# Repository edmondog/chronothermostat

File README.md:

# chronothermostat
Homebrewed room by room themperature control

Very rough i2c control for the temperature sensor (texas tmp 102 http://www.ti.com.cn/cn/lit/ds/symlink/tmp102.pdf)
The board has:
4 digit 7seg led display
1 encoder
1 pushbutton
485 serial interface
2 tempeature sensors
1 AC triac switch
ATMEGA328p cpu

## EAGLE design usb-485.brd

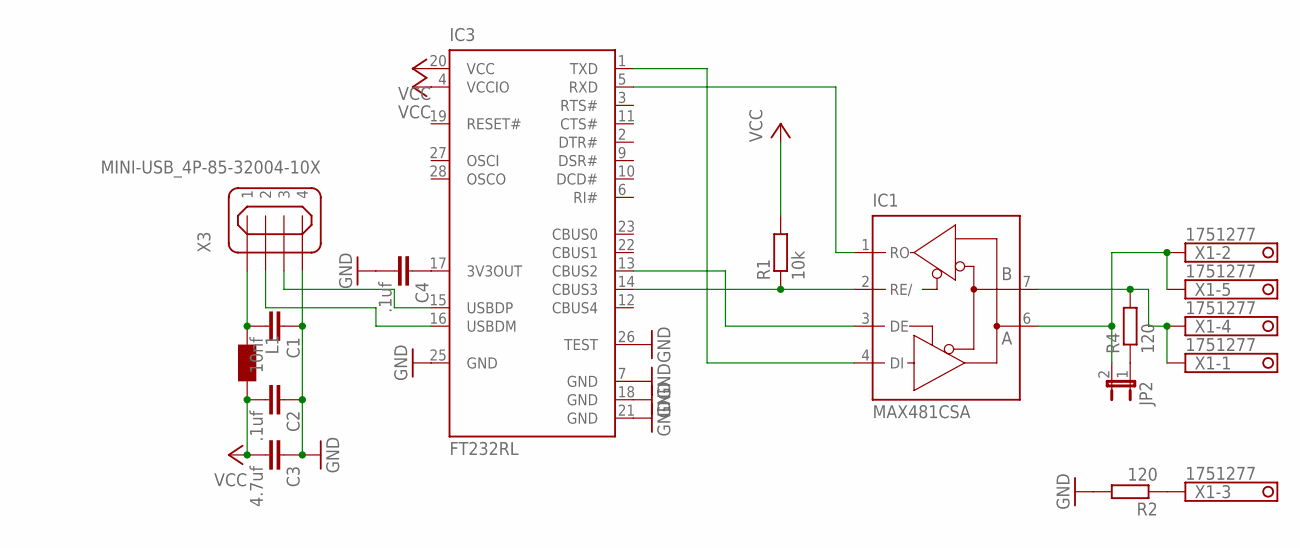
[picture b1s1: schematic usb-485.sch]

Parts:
C1: 10nf; C0805
C2, C4: .1uf; C1206
C3: 4.7uf; C1206
IC1: MAX481CSA; SO08
IC3: FT232RL; SSOP28
JP2: JP1E; JP1
L1: WE-CBF_1206; 1206
R1: 10k; 0207/10
R2, R4: 120; 0207/10
X1: 1751277
X3: MINI-USB_4P-85-32004-10X; 85-32004-10X

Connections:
GND: C1.1, C2.1, C3.1, C4.2, IC1.5 (GND), IC3.7 (GND), IC3.18 (GND), IC3.21 (GND), IC3.25 (GND), IC3.26 (TEST), R2.2, X3.4
unnamed: IC1.3 (DE), IC3.13 (CBUS2)
unnamed: IC1.2 (RE/), IC3.14 (CBUS3), R1.1
unnamed: IC1.7 (B), R4.2, X1.1, X1.4
unnamed: R2.1, X1.3
unnamed: JP2.1, R4.1
unnamed: C1.2, L1.1, X3.1
unnamed: IC1.6 (A), JP2.2, X1.2, X1.5
unnamed: IC3.16 (USBDM), X3.2
unnamed: IC3.15 (USBDP), X3.3
unnamed: C4.1, IC3.17 (3V3OUT)
unnamed: IC1.1 (RO), IC3.5 (RXD)
unnamed: IC1.4 (DI), IC3.1 (TXD)
VCC: C2.2, C3.2, IC1.8 (VCC), IC3.4 (VCCIO), IC3.20 (VCC), L1.2, R1.2

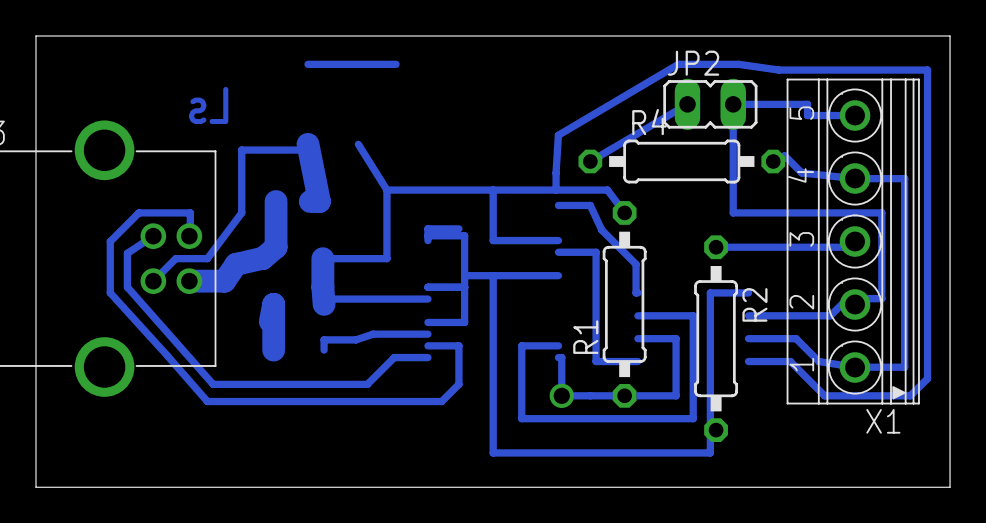
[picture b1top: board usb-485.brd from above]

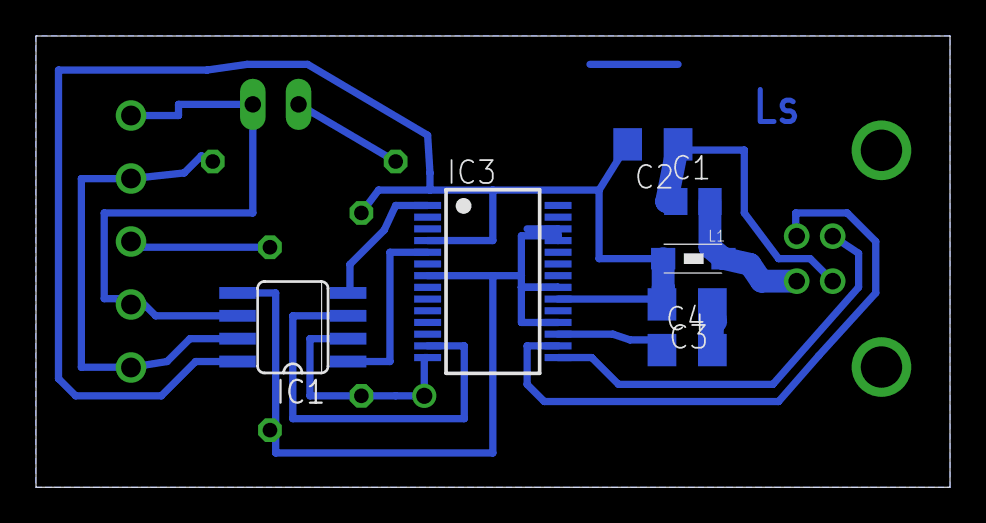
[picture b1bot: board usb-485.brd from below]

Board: 2 copper layers, 50.8 x 25.1 mm, 13 parts (7 on the bottom side), 14 nets.

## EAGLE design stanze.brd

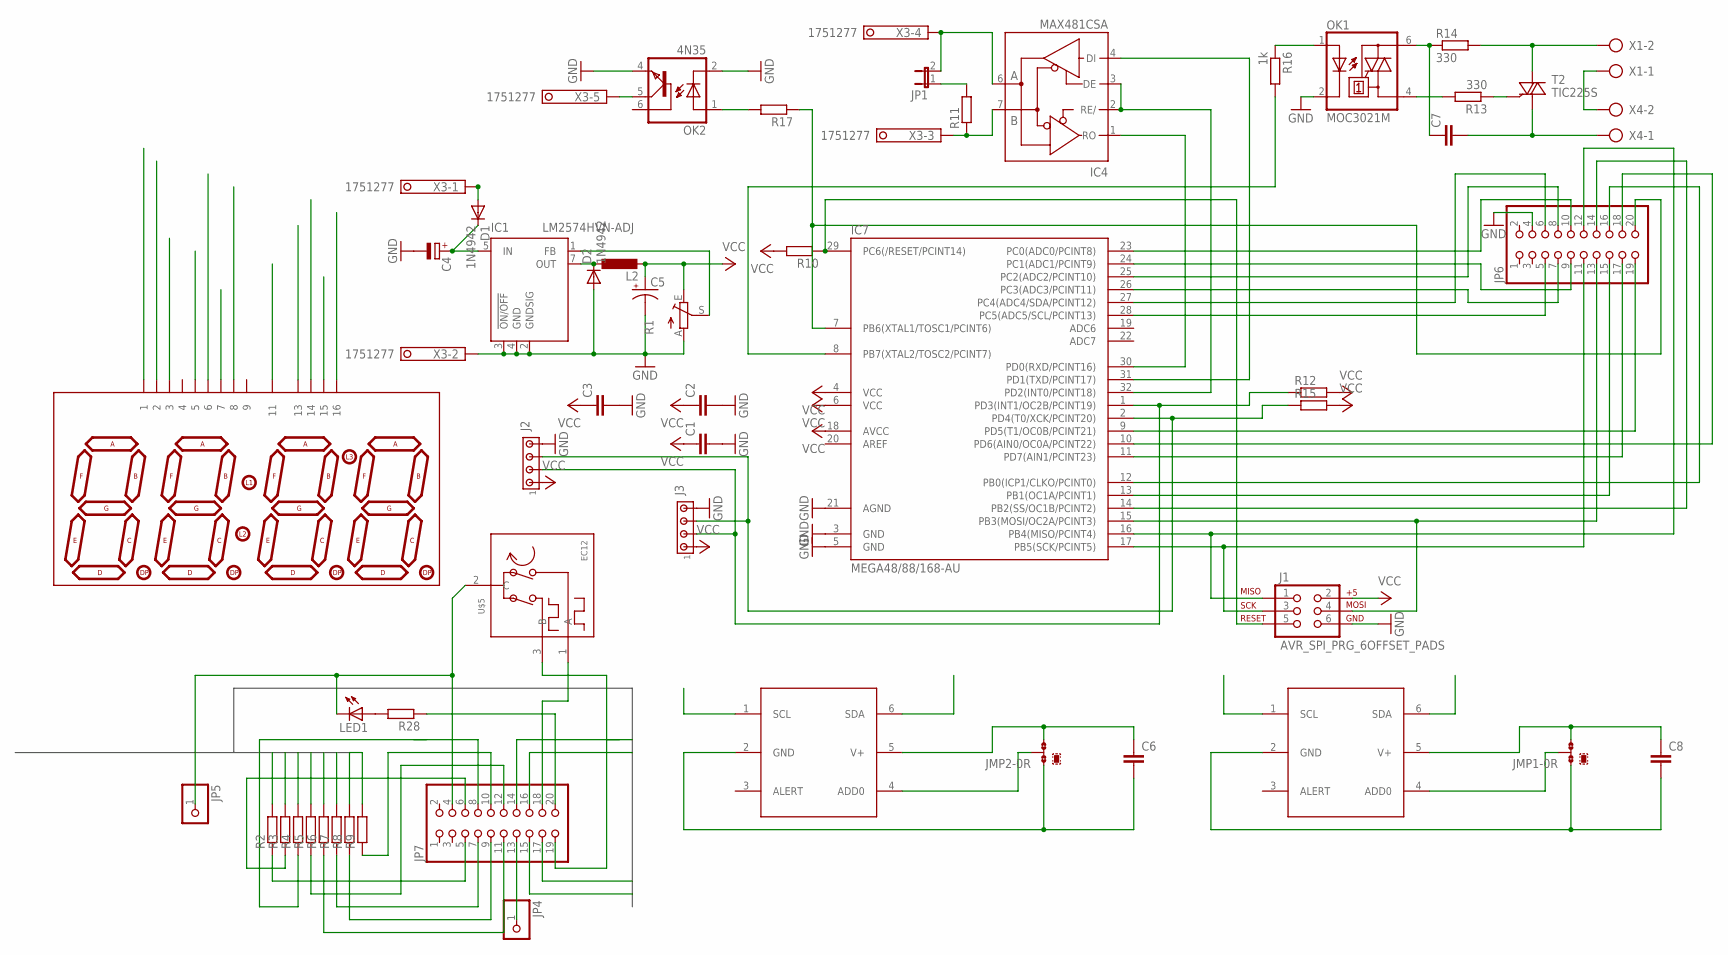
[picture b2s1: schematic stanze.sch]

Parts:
C1, C2, C3: C-EUC1206; C1206
C4: CPOL-EUE2,5-6E; E2,5-6E
C5: CPOL-USE5-10.5; E5-10,5
C6, C8: C-EUC0805; C0805
C7: C-EU075-032X103; C075-032X103
D1, D2: 1N4942; DO41-10
IC1: LM2574HVN-ADJ; DIL08
IC4: MAX481CSA; SO08; MPN MAX481CSA
IC7: MEGA48/88/168-AU; TQFP32-08
J1: AVR_SPI_PRG_6OFFSET_PADS; 2X3_OFFSET
J2, J3: MTA04-100; 10X04MTA
JMP1, JMP2: 0R-JUMPA; A0R-JMP
JP1: JP1E; JP1
JP4, JP5: PINHD-1X1; 1X01
JP6, JP7: PINHD-2X10; 2X10
L2: L-EUTFI0305; TFI0305
LED1: LED5MM
OK1: MOC3021M; DIL06
OK2: 4N35; DIL06
R1: TRIM_EU-B64Y; B64Y
R2, R3, R4, R5, R6, R7, R8, R9, R10, R11, R12, R15, R17, R28: R-EU_0207/10; 0207/10
R13, R14: 330; 0207/10
R16: 1k; 0207/10
T2: TIC225S; TO220DS
U$1, U$2: TMP112; SOT563
U$3: 7-SEGMENT-4DIGITPTH; 7-SEGMENT-4DIGIT
U$5: EC12
X1, X4: AK500/2
X3: 1751277

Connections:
DISPLAY1: R2.2, U$3.14
DISPLAY2: R3.2, U$3.16
DISPLAY3: R4.2, U$3.13
DISPLAY4: R5.2, U$3.3
DISPLAY5: R6.2, U$3.5
DISPLAY6: R7.2, U$3.11
DISPLAY7: R8.2, U$3.15
DISPLAY8: R9.2, U$3.7
GND: C1.2, C2.2, C3.2, C4.-, C5.-, D2.A, IC1.2 (GNDSIG), IC1.3 (!ON/OFF), IC1.4 (GND), IC4.5 (GND), IC7.3 (GND), IC7.5 (GND), IC7.21 (AGND), J1.6, J2.4, J3.4, JP6.4, OK1.2 (C), OK2.2 (C), OK2.4 (EMI), R1.A, X3.2
unnamed: C7.1, OK1.6 (A2), R14.1
unnamed: JMP2.2, U$1.4 (ADD0)
unnamed: IC7.9 (PD5(T1/OC0B/PCINT21)), JP6.19
unnamed: IC7.10 (PD6(AIN0/OC0A/PCINT22)), JP6.18
unnamed: IC7.1 (PD3(INT1/OC2B/PCINT19)), J2.2, J3.2, R12.1
unnamed: IC7.2 (PD4(T0/XCK/PCINT20)), J2.3, J3.3, R15.1
unnamed: OK2.1 (A), R17.2
unnamed: IC7.8 (PB7(XTAL2/TOSC2/PCINT7)), R16.2
unnamed: IC7.7 (PB6(XTAL1/TOSC1/PCINT6)), JP6.20, R17.1
unnamed: IC7.17 (PB5(SCK/PCINT5)), J1.3, JP6.11
unnamed: IC7.29 (PC6(/RESET/PCINT14)), J1.5, R10.1
unnamed: C8.1, JMP1.3, U$2.5 (V+)
unnamed: IC7.11 (PD7(AIN1/PCINT23)), JP6.17
unnamed: JP7.5, R2.1
unnamed: IC7.15 (PB3(MOSI/OC2A/PCINT3)), J1.4, JP6.13
unnamed: OK2.5 (COL), X3.5
unnamed: IC7.12 (PB0(ICP1/CLKO/PCINT0)), JP6.16
unnamed: IC7.13 (PB1(OC1A/PCINT1)), JP6.15
unnamed: IC7.14 (PB2(SS/OC1B/PCINT2)), JP6.14
unnamed: IC7.23 (PC0(ADC0/PCINT8)), JP6.10
unnamed: IC7.28 (PC5(ADC5/SCL/PCINT13)), JP6.5
unnamed: JP7.6, R3.1
unnamed: R13.1, T2.G
unnamed: C6.1, JMP2.3, U$1.5 (V+)
unnamed: IC7.24 (PC1(ADC1/PCINT9)), JP6.9
unnamed: OK1.4 (A1), R13.2
unnamed: IC4.4 (DI), IC7.31 (PD1(TXD/PCINT17))
unnamed: IC4.1 (RO), IC7.30 (PD0(RXD/PCINT16))
unnamed: IC4.2 (RE/), IC4.3 (DE), IC7.32 (PD2(INT0/PCINT18))
unnamed: JP7.18, U$5.1 (A)
unnamed: IC7.26 (PC3(ADC3/PCINT11)), JP6.7
unnamed: IC4.7 (B), R11.1, X3.3
unnamed: IC4.6 (A), JP1.2, X3.4
unnamed: D2.C, IC1.7 (OUT), L2.1
unnamed: IC1.1 (FB), R1.S
unnamed: C4.+, D1.C, IC1.5 (IN)
unnamed: JP1.1, R11.2
unnamed: D1.A, X3.1
unnamed: IC7.25 (PC2(ADC2/PCINT10)), JP6.8
unnamed: JP7.7, R7.1
unnamed: R14.2, T2.A2, X1.2
unnamed: IC7.16 (PB4(MISO/PCINT4)), J1.1, JP6.12
unnamed: JP7.8, R4.1
unnamed: JP7.9, R8.1
unnamed: JP7.10, R9.1
unnamed: JP7.11, R6.1
unnamed: JP7.12, R5.1
unnamed: JP4.1, JP7.13
unnamed: C7.2, T2.A1, X4.1
unnamed: X1.1, X4.2
unnamed: OK1.1 (A), R16.1
unnamed: IC7.27 (PC4(ADC4/SDA/PCINT12)), JP6.6
unnamed: JP7.19, U$5.3 (B)
unnamed: JP5.1, JP7.4, LED1.K (C), U$5.2 (C)
unnamed: JP7.20, R28.1
unnamed: LED1.A, R28.2
unnamed: C6.2, JMP2.1, U$1.2 (GND)
unnamed: JMP1.2, U$2.4 (ADD0)
unnamed: C8.2, JMP1.1, U$2.2 (GND)
S1: JP7.14, U$3.1
S2: JP7.15, U$3.2
S3: JP7.16, U$3.6
S4: JP7.17, U$3.8
VCC: C1.1, C2.1, C3.1, C5.+, IC4.8 (VCC), IC7.4 (VCC), IC7.6 (VCC), IC7.18 (AVCC), J1.2, J2.1, J3.1, L2.2, R1.E, R10.2, R12.2, R15.2

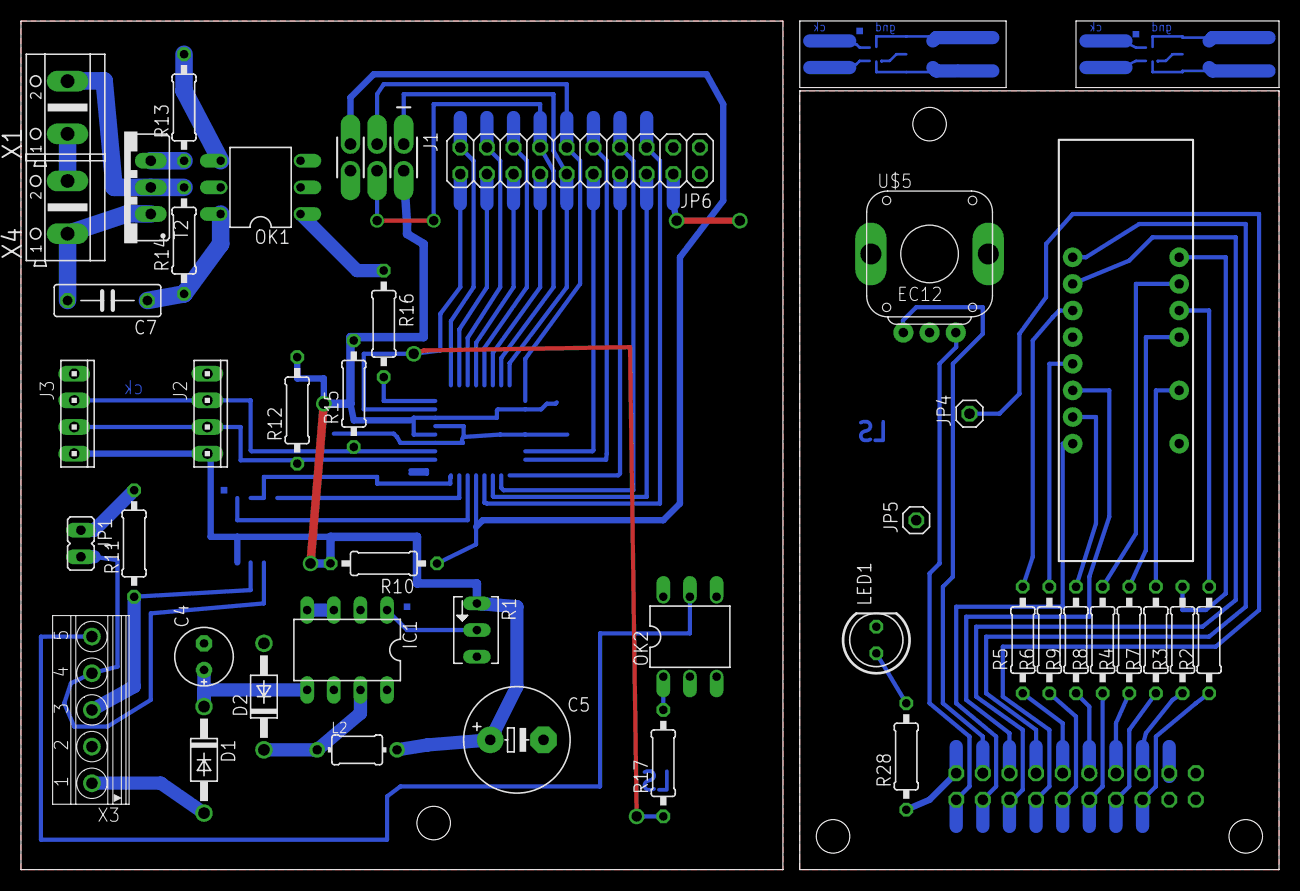
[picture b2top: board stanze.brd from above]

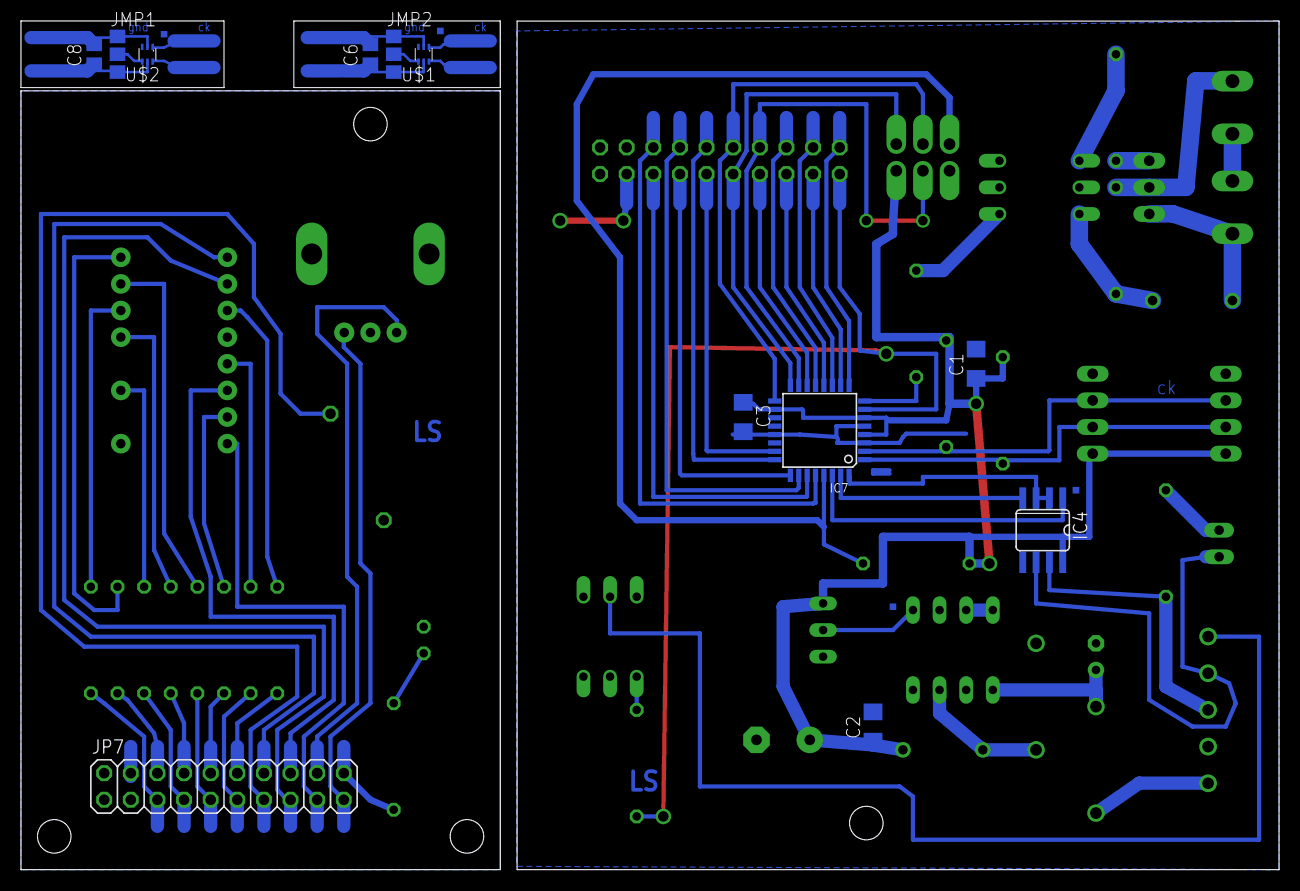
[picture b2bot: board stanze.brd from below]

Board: 2 copper layers, 120.0 x 81.0 mm, 53 parts (12 on the bottom side), 73 nets.

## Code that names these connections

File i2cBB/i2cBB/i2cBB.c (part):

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
#define RS485DIR_DDR DDRD
#define RS485DIR_PORT PORTD
#define RS485DIR_BIT PD2

#define OUT_0 PB7
#define OUT_0_PORT PORTB
#define OUT_0_DDR DDRB
#define LED_1 PB6
#define LED_1_PORT PORTB
#define LED_1_DDR DDRB
#define ENABLE_0 PD7
#define ENABLE_0_PORT PORTD
#define ENABLE_0_DDR DDRD
#define ENABLE_1 PB0
#define ENABLE_1_PORT PORTB
#define ENABLE_1_DDR DDRB
#define ENABLE_2 PB1
#define ENABLE_2_PORT PORTB
#define ENABLE_2_DDR DDRB
#define ENABLE_3 PB2
#define ENABLE_3_PORT PORTB
#define ENABLE_3_DDR DDRB
#define FASE_1 PD6
#define FASE_1_PORT PORTD
#define FASE_1_PIN PIND
#define FASE_1_DDR DDRD
#define FASE_2 PD5
#define FASE_2_PORT PORTD
#define FASE_2_PIN PIND
#define FASE_2_DDR DDRD
#define PULS PB3
#define PULS_PORT PORTB
#define PULS_PIN PINB
#define PULS_DDR DDRB
#define SEG_A PC5
#define SEG_A_PORT PORTC
#define SEG_A_DDR DDRC
#define SEG_B PC4
#define SEG_B_PORT PORTC
#define SEG_B_DDR DDRC
#define SEG_C PC2
#define SEG_C_PORT PORTC
#define SEG_C_DDR DDRC
#define SEG_D PB4
#define SEG_D_PORT PORTB
#define SEG_D_DDR DDRB
#define SEG_E PB5
#define SEG_E_PORT PORTB
#define SEG_E_DDR DDRB
#define SEG_F PC3
#define SEG_F_PORT PORTC
#define SEG_F_DDR DDRC
#define SEG_G PC1
#define SEG_G_PORT PORTC
#define SEG_G_DDR DDRC
#define SEG_P PC0
#define SEG_P_PORT PORTC
#define SEG_P_DDR DDRC
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

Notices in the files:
parts and their libraries:
SparkFun: Licensing: CC v3.0 Share-Alike You are welcome to use this library for commercial purposes.
